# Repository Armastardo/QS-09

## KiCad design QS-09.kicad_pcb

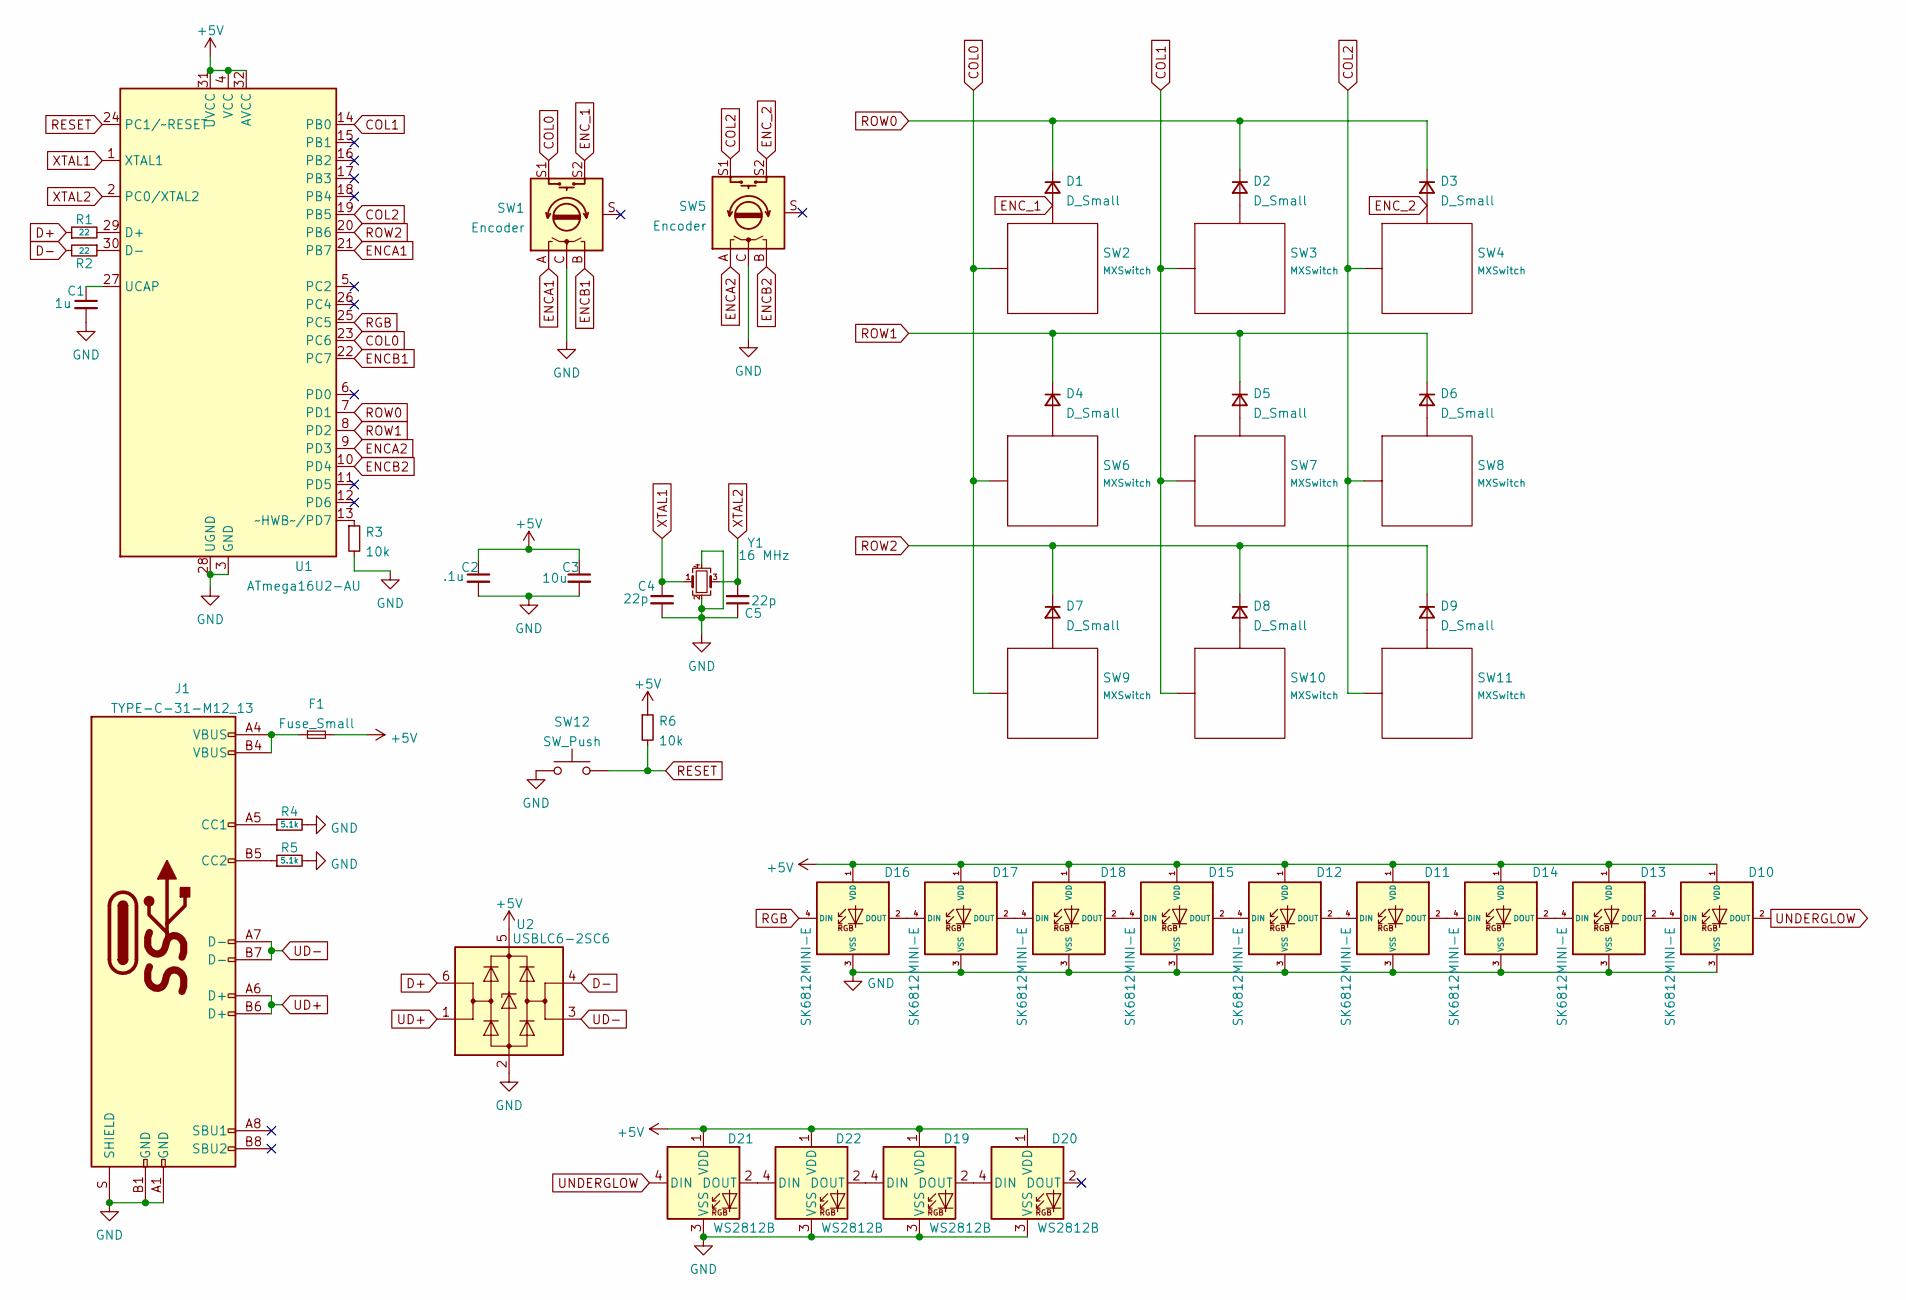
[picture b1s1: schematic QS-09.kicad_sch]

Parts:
C1: 1u; C_0603_1608Metric
C2: .1u; C_0603_1608Metric
C3: 10u; C_0603_1608Metric
C4, C5: 22p; C_0603_1608Metric
D1, D2, D3, D4, D5, D6, D7, D8, D9: D_Small; D_SOD-123
D10, D11, D12, D13, D14, D15, D16, D17, D18: SK6812MINI-E; SK6812MINI_3535_6028_3.2x2.8mm_Round; MPN SK812MINI-E
D19, D20, D21, D22: WS2812B; LED_WS2812B_PLCC4_5.0x5.0mm_P3.2mm
F1: Fuse_Small; Fuse_1206_3216Metric
J1: TYPE-C-31-M12_13; TYPE-C-31-M-12
R1, R2: 22; R_0603_1608Metric
R3, R6: 10k; R_0603_1608Metric
R4, R5: 5.1k; R_0603_1608Metric
SW1, SW5: Encoder; RotaryEncoder_Alps_EC11E-Switch_Vertical_H20mm
SW2, SW3, SW4, SW6, SW7, SW8, SW9, SW10, SW11: MXSwitch; MX100
SW12: SW_Push; SW_SPST_SKQG_WithStem
U1: ATmega16U2-AU; TQFP-32_7x7mm_P0.8mm
U2: USBLC6-2SC6; SOT-23-6
Y1: 16 MHz; Crystal_SMD_3225-4Pin_3.2x2.5mm

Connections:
+5V: C2.1, C3.1, D10.1 (VDD), D11.1 (VDD), D12.1 (VDD), D13.1 (VDD), D14.1 (VDD), D15.1 (VDD), D16.1 (VDD), D17.1 (VDD), D18.1 (VDD), D19.1 (VDD), D20.1 (VDD), D21.1 (VDD), D22.1 (VDD), F1.2, R6.1, U1.4 (VCC), U1.31 (UVCC), U1.32 (AVCC), U2.5 (VBUS)
COL0: SW1.S1, SW2.1 (Col), SW6.1 (Col), SW9.1 (Col), U1.23 (PC6)
COL1: SW3.1 (Col), SW7.1 (Col), SW10.1 (Col), U1.14 (PB0)
COL2: SW4.1 (Col), SW5.S1, SW8.1 (Col), SW11.1 (Col), U1.19 (PB5)
D+: R1.1, U2.6 (I/O1)
D-: R2.2, U2.4 (I/O2)
ENCA1: SW1.A, U1.21 (PB7)
ENCA2: SW5.A, U1.9 (PD3)
ENCB1: SW1.B, U1.22 (PC7)
ENCB2: SW5.B, U1.10 (PD4)
ENC_1: D1.2 (A), SW1.S2, SW2.2 (Row)
ENC_2: D3.2 (A), SW4.2 (Row), SW5.S2
GND: C1.2, C2.2, C3.2, C4.2, C5.1, D10.3 (VSS), D11.3 (VSS), D12.3 (VSS), D13.3 (VSS), D14.3 (VSS), D15.3 (VSS), D16.3 (VSS), D17.3 (VSS), D18.3 (VSS), D19.3 (VSS), D20.3 (VSS), D21.3 (VSS), D22.3 (VSS), J1.A1 (GND), J1.B1 (GND), J1.S (SHIELD), R3.2, R4.2, R5.2, SW1.C, SW5.C, SW12.1, U1.3 (GND), U1.28 (UGND), U2.2 (GND), Y1.2, Y1.4
unnamed: C1.1, U1.27 (UCAP)
unnamed: D2.2 (A), SW3.2 (Row)
unnamed: D4.2 (A), SW6.2 (Row)
unnamed: D5.2 (A), SW7.2 (Row)
unnamed: D6.2 (A), SW8.2 (Row)
unnamed: D7.2 (A), SW9.2 (Row)
unnamed: D8.2 (A), SW10.2 (Row)
unnamed: D9.2 (A), SW11.2 (Row)
unnamed: D10.4 (DIN), D13.2 (DOUT)
unnamed: D11.2 (DOUT), D14.4 (DIN)
unnamed: D11.4 (DIN), D12.2 (DOUT)
unnamed: D12.4 (DIN), D15.2 (DOUT)
unnamed: D13.4 (DIN), D14.2 (DOUT)
unnamed: D15.4 (DIN), D18.2 (DOUT)
unnamed: D16.2 (DOUT), D17.4 (DIN)
unnamed: D17.2 (DOUT), D18.4 (DIN)
unnamed: D19.2 (DOUT), D20.4 (DIN)
unnamed: D19.4 (DIN), D22.2 (DOUT)
unnamed: D21.2 (DOUT), D22.4 (DIN)
unnamed: F1.1, J1.A4 (VBUS), J1.B4 (VBUS)
unnamed: J1.A5 (CC1), R4.1
unnamed: J1.B5 (CC2), R5.1
unnamed: R1.2, U1.29 (D+)
unnamed: R2.1, U1.30 (D-)
unnamed: R3.1, U1.13 (~HWB~/PD7)
RESET: R6.2, SW12.2, U1.24 (PC1/~RESET)
RGB: D16.4 (DIN), U1.25 (PC5)
ROW0: D1.1 (K), D2.1 (K), D3.1 (K), U1.7 (PD1)
ROW1: D4.1 (K), D5.1 (K), D6.1 (K), U1.8 (PD2)
ROW2: D7.1 (K), D8.1 (K), D9.1 (K), U1.20 (PB6)
UD+: J1.A6 (D+), J1.B6 (D+), U2.1 (I/O1)
UD-: J1.A7 (D-), J1.B7 (D-), U2.3 (I/O2)
UNDERGLOW: D10.2 (DOUT), D21.4 (DIN)
XTAL1: C4.1, U1.1 (XTAL1), Y1.1
XTAL2: C5.2, U1.2 (PC0/XTAL2), Y1.3

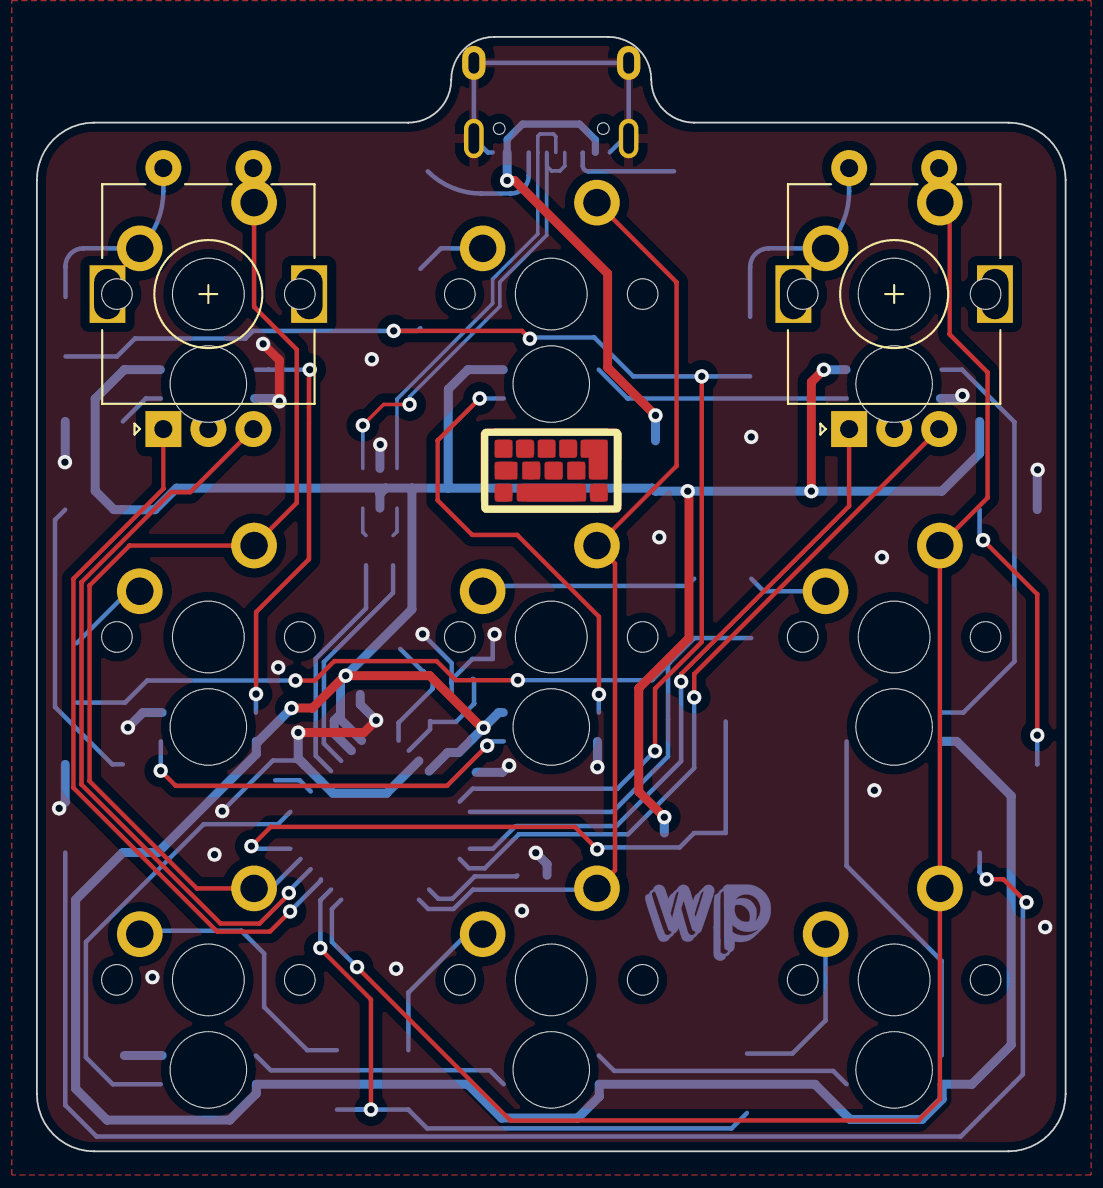
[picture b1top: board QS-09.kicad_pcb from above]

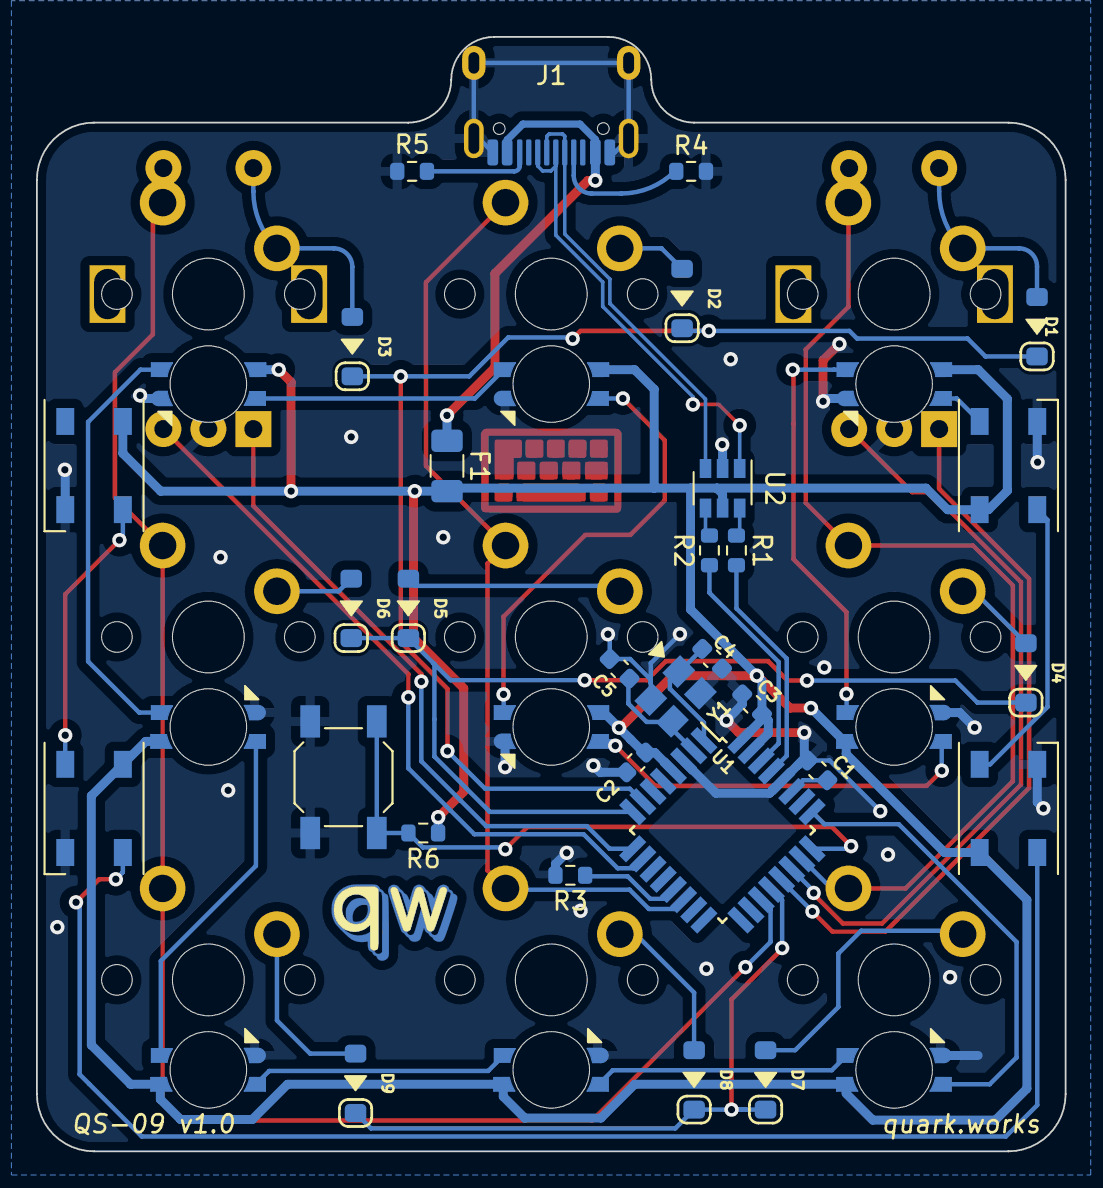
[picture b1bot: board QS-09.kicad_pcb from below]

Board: 2 copper layers, 57.2 x 61.9 mm, 52 parts (49 on the bottom side), 48 nets.

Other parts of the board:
Ref**: Val**; iso
Ref**#2: Val**; qw-logo-small

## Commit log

2021-08-09 Pre routing
2021-08-09 USB ready, fixed RGB
2021-08-10 alpha
2021-09-05 Added reset button, fixed a missing resistor
2021-11-12 Fixed some wonky shit with the data lines
2021-12-31 Ready for production
2022-02-02 New logo, version 1.0
2022-06-30 Added case
